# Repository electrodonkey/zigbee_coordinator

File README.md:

# BHive
TI CC2652 Zigbee coordinator/node in a breakout board form

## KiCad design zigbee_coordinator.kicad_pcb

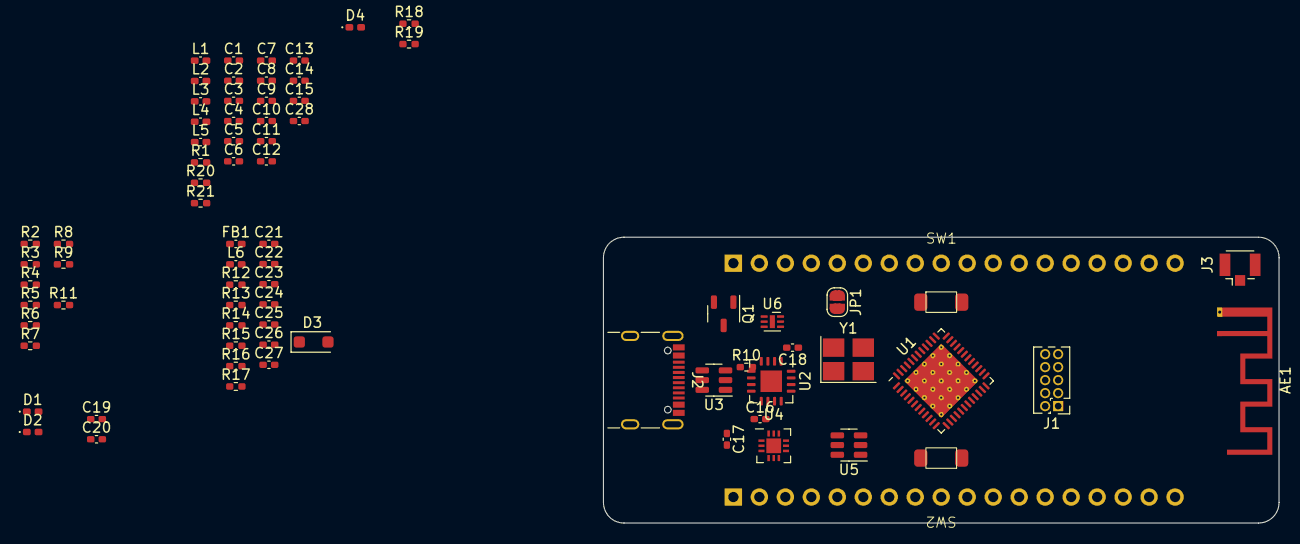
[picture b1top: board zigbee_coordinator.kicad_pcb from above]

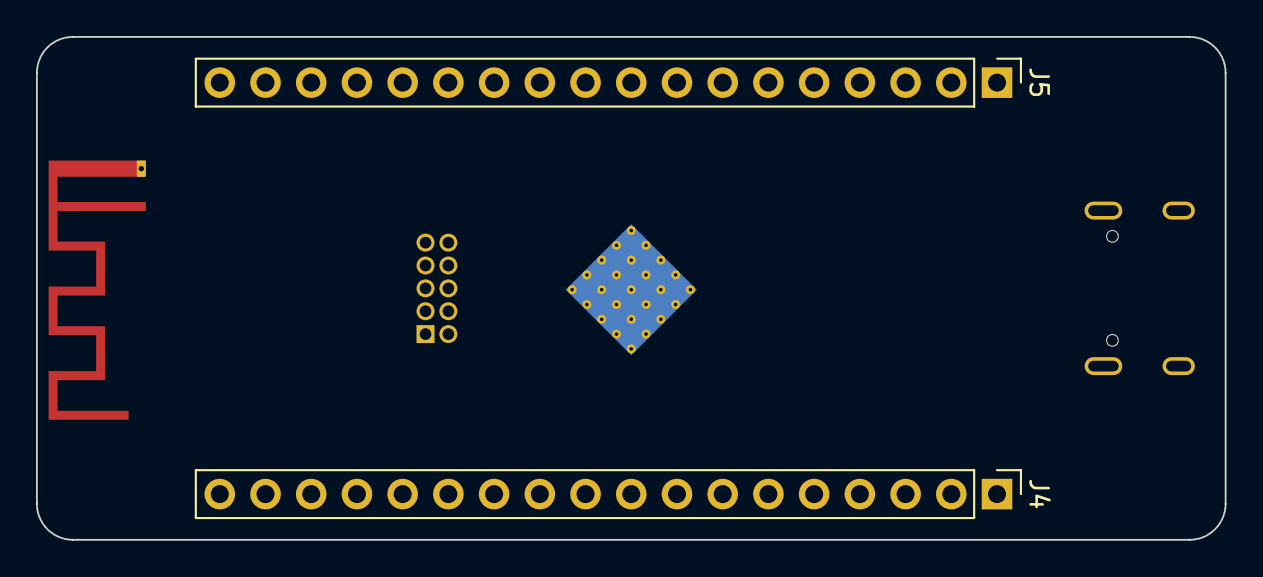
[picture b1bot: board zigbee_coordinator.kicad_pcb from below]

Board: 4 copper layers, 66.0 x 27.9 mm, 77 parts (2 on the bottom side), 79 nets, no tracks yet.

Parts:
AE1: Antenna; Texas_SWRA117D_2.4GHz_Right
C1, C2, C3, C5, C7, C8, C10, C16, C18, C24, C27: 100n; C_0402_1005Metric_Pad0.74x0.62mm_HandSolder
C4, C6, C23: 22u; C_0402_1005Metric_Pad0.74x0.62mm_HandSolder
C9, C12, C28: 12p; C_0402_1005Metric_Pad0.74x0.62mm_HandSolder
C11, C13, C14: 1p; C_0402_1005Metric_Pad0.74x0.62mm_HandSolder
C15, C25, C26: 1u; C_0402_1005Metric_Pad0.74x0.62mm_HandSolder
C17: 4.7u; C_0402_1005Metric_Pad0.74x0.62mm_HandSolder
C19, C20: 47p; C_0402_1005Metric_Pad0.74x0.62mm_HandSolder
C21: 10n; C_0402_1005Metric_Pad0.74x0.62mm_HandSolder
C22: 10u; C_0402_1005Metric_Pad0.74x0.62mm_HandSolder
D1: LED_RX; LED_0402_1005Metric_Pad0.77x0.64mm_HandSolder
D2: LED_TX; LED_0402_1005Metric_Pad0.77x0.64mm_HandSolder
D3: MBR120VLSFT1G; D_SOD-123F
D4: USER_LED; LED_0402_1005Metric_Pad0.77x0.64mm_HandSolder
FB1: 100R@100MHz; L_0402_1005Metric_Pad0.77x0.64mm_HandSolder
J1: Conn_ARM_JTAG_SWD_10; PinHeader_2x05_P1.27mm_Vertical
J2: USB_C_Receptacle_USB2.0; USB_C_Receptacle_GCT_USB4105-xx-A_16P_TopMnt_Horizontal
J3: u.FL; U.FL_Hirose_U.FL-R-SMT-1_Vertical
J4, J5: Conn_01x18; PinHeader_1x18_P2.54mm_Vertical
JP1: LDO_ON; SolderJumper-2_P1.3mm_Open_RoundedPad1.0x1.5mm
L1: 6.8uH; L_0402_1005Metric_Pad0.77x0.64mm_HandSolder
L2, L5: 3.7nH; L_0402_1005Metric_Pad0.77x0.64mm_HandSolder
L3, L4: 3.4nH; L_0402_1005Metric_Pad0.77x0.64mm_HandSolder
L6: 1uH; L_0402_1005Metric_Pad0.77x0.64mm_HandSolder
Q1: DMG2305UX-7; SOT-23-3
R1, R4, R5, R14, R17, R18: 100k; R_0402_1005Metric_Pad0.72x0.64mm_HandSolder
R2, R3: 5k1; R_0402_1005Metric_Pad0.72x0.64mm_HandSolder
R6, R7, R20, R21: 0R; R_0402_1005Metric_Pad0.72x0.64mm_HandSolder
R8, R9, R19: 330R; R_0402_1005Metric_Pad0.72x0.64mm_HandSolder
R10, R11: 27R; R_0402_1005Metric_Pad0.72x0.64mm_HandSolder
R12: 96k@1%; R_0402_1005Metric_Pad0.72x0.64mm_HandSolder
R13: 54.9k@1%; R_0402_1005Metric_Pad0.72x0.64mm_HandSolder
R15: 7.5k@1%; R_0402_1005Metric_Pad0.72x0.64mm_HandSolder
R16: 10k@1%; R_0402_1005Metric_Pad0.72x0.64mm_HandSolder
SW1, SW2: SW_Push; TL1017AABF160QG
U1: cc2652r7; VQFN-48-1EP_7x7mm_P0.5mm_EP5.15x5.15mm_ThermalVias
U2: FT230XQ; QFN-16-1EP_4x4mm_P0.65mm_EP2.1x2.1mm
U3: USBLC6-2SC6; SOT-23-6
U4: ISL9120IRTNZ; QFN-12_EP_3x3_Pitch0.5mm
U5: TPL5111; SOT-23-6
U6: MIC5353-3.3YMT; MLF-6-1EP_1.6x1.6mm_P0.5mm_EP0.5x1.26mm
Y1: ECS-480-7-33B2-CTN-TR3; Crystal_SMD_3225-4Pin_3.2x2.5mm_HandSoldering

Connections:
+3V3: C1.1, C2.1, C3.1, C4.1, C5.1, C23.2, C24.2, C26.2, J1.1 (VTref), J5.3, R1.1, R17.2, R18.1, R19.2, U1.13 (VDDS2), U1.22 (VDDS3), U1.34 (VDDS_DCDC), U1.44 (VDDS), U4.10 (FB), U4.11 (VOUT), U5.1 (VDD), U6.4 (VOUT)
+5V: C16.2, C17.1, D3.2 (A), FB1.2, J5.5, JP1.1 (A), Q1.2 (G), U2.10 (VCC)
/power_block/V_SYS: C22.2, D3.1 (K), Q1.3 (S), R14.2, R15.2, U4.5 (VIN), U4.6 (VIN)
BAT_MON: R15.1, R16.2
DCDC_SW: L1.1, U1.33 (DCDC_SW)
DELAY: R12.2, R13.2, U5.3 (DELAY/M_DRV)
DIO0_0: J4.1, U1.5 (DIO_0)
DIO0_1: J4.2, U1.6 (DIO_1)
DIO2_RX: J4.3, R4.2, R6.1, U1.7 (DIO_2)
DIO3_TX: J4.4, R5.2, R7.1, U1.8 (DIO_3)
DIO4_SCL: J4.5, U1.9 (DIO_4)
DIO5_SDA: J4.6, U1.10 (DIO_5)
DIO8_MISO: J4.9, U1.14 (DIO_8)
DIO9_MOSI: J4.10, U1.15 (DIO_9)
DIO10_SCLK: J4.11, U1.16 (DIO_10)
DIO11_CS: J4.12, U1.17 (DIO_11)
DIO_12: J4.13, U1.18 (DIO_12)
DIO_13: J4.14, U1.19 (DIO_13)
DIO_14: J4.15, U1.20 (DIO_14)
DIO_15: J4.16, U1.21 (DIO_15)
DIO_18: J5.6, U1.28 (DIO_18)
DIO_19: J5.7, U1.29 (DIO_19)
DIO_20: J5.8, U1.30 (DIO_20)
DIO_21: J5.9, U1.31 (DIO_21)
DIO_22: J5.10, U1.32 (DIO_22)
DIO_23: J5.11, U1.36 (DIO_23)
DIO_24: J5.12, U1.37 (DIO_24)
DIO_25: J5.13, U1.38 (DIO_25)
DIO_26: J5.14, U1.39 (DIO_26)
DIO_27: J5.15, U1.40 (DIO_27)
DIO_28: J5.16, U1.41 (DIO_28)
DIO_29: J5.17, U1.42 (DIO_29)
DIO_30: J5.18, U1.43 (DIO_30)
FTDI_3V3: C18.2, R4.1, R5.1, R8.2, R9.2, U2.1 (VCCIO), U2.8 (3V3OUT), U2.9 (~RESET)
GND: C1.2, C2.2, C3.2, C4.2, C5.2, C6.2, C7.2, C8.2, C9.1, C10.2, C13.1, C14.2, C15.2, C16.1, C17.2, C18.1, C19.1, C20.1, C21.1, C22.1, C23.1, C24.1, C25.1, C26.1, C27.1, J1.3 (GND), J1.5 (GND), J1.9 (GNDDetect), J2.A1 (GND), J2.A12 (GND), J2.B1 (GND), J2.B12 (GND), J2.S1 (SHIELD), J5.2, J5.4, R2.2, R3.2, R12.1, R13.1, R16.1, R20.2, R21.2, SW1.1, SW2.1, U1.49 (EGP), U2.3 (GND), U2.13 (GND), U2.17 (GND), U3.2 (GND), U4.2 (PGND), U4.7 (BYPS), U4.8 (GND), U4.13 (EPD), U5.2 (GND), U6.2 (GND), U6.7 (GND)
JTAG_TCK: J1.4 (SWDCLK/TCK), U1.25 (JTAG_TCKC)
JTAG_TDI: J1.8 (NC/TDI), U1.27 (DIO_17)
JTAG_TDO: J1.6 (SWO/TDO), U1.26 (DIO_16)
JTAG_TMS: J1.2 (SWDIO/TMS), U1.24 (JTAG_TMSC)
unnamed: AE1.1 (A), C12.1
unnamed: C9.2, L2.2
unnamed: C11.2, L3.1, L5.2
unnamed: C12.2, C28.2, L4.2
unnamed: C13.2, L3.2, L4.1
unnamed: D1.2 (A), R8.1
unnamed: D1.1 (K), U2.11 (CBUS1)
unnamed: D2.2 (A), R9.1
unnamed: D2.1 (K), U2.5 (CBUS2)
unnamed: D4.2 (A), R19.1
unnamed: J2.A5 (CC1), R3.1
unnamed: J2.B5 (CC2), R2.1
unnamed: C28.1, J3.1 (In)
unnamed: C25.2, JP1.2 (B), U6.1 (EN), U6.3 (VIN)
unnamed: L6.1, U4.3 (LX1), U4.4 (LX1)
unnamed: L6.2, U4.1 (LX2), U4.12 (LX2)
unnamed: R20.1, Y1.4
unnamed: R21.1, Y1.2
unnamed: C15.1, U1.23 (DCOUPL)
unnamed: C14.1, L5.1, U1.2 (RF_N)
unnamed: C11.1, L2.1, U1.1 (RF_P)
unnamed: U1.46 (X48M_N), Y1.3
unnamed: U1.47 (X48M_P), Y1.1
unnamed: R7.2, U2.2 (RXD)
unnamed: R6.2, U2.15 (TXD)
unnamed: C19.2, R10.2, U2.7 (USBDM)
unnamed: C20.2, R11.2, U2.6 (USBDP)
unnamed: C27.2, U6.6 (BYP)
RST_N: C10.1, J1.10 (~RESET), R1.2, SW1.2, U1.35 (RST_N)
TIMER_EN: R17.1, U5.6 (EN/ONE_SHOT)
USB_CON_D+: J2.A6 (D+), J2.B6 (D+), U3.6 (I/O1)
USB_CON_D-: J2.A7 (D-), J2.B7 (D-), U3.4 (I/O2)
USB_FTDI_D+: R11.1, U3.1 (I/O1)
USB_FTDI_D-: R10.1, U3.3 (I/O2)
USER_BTN: J4.8, R18.2, SW2.2, U1.12 (DIO_7)
USER_LED: D4.1 (K), J4.7, U1.11 (DIO_6)
VBAT: J5.1, Q1.1 (D)
VBUS: C21.2, FB1.1, J2.A4 (VBUS), J2.A9 (VBUS), J2.B4 (VBUS), J2.B9 (VBUS), U3.5 (VBUS)
VDDR: C6.1, C7.1, C8.1, L1.2, U1.45 (VDDR), U1.48 (VDDR_RF)
VREG_EN: J4.17, R14.1, U4.9 (EN), U5.5 (~DRV)

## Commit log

2024-03-25 Add initial work files
